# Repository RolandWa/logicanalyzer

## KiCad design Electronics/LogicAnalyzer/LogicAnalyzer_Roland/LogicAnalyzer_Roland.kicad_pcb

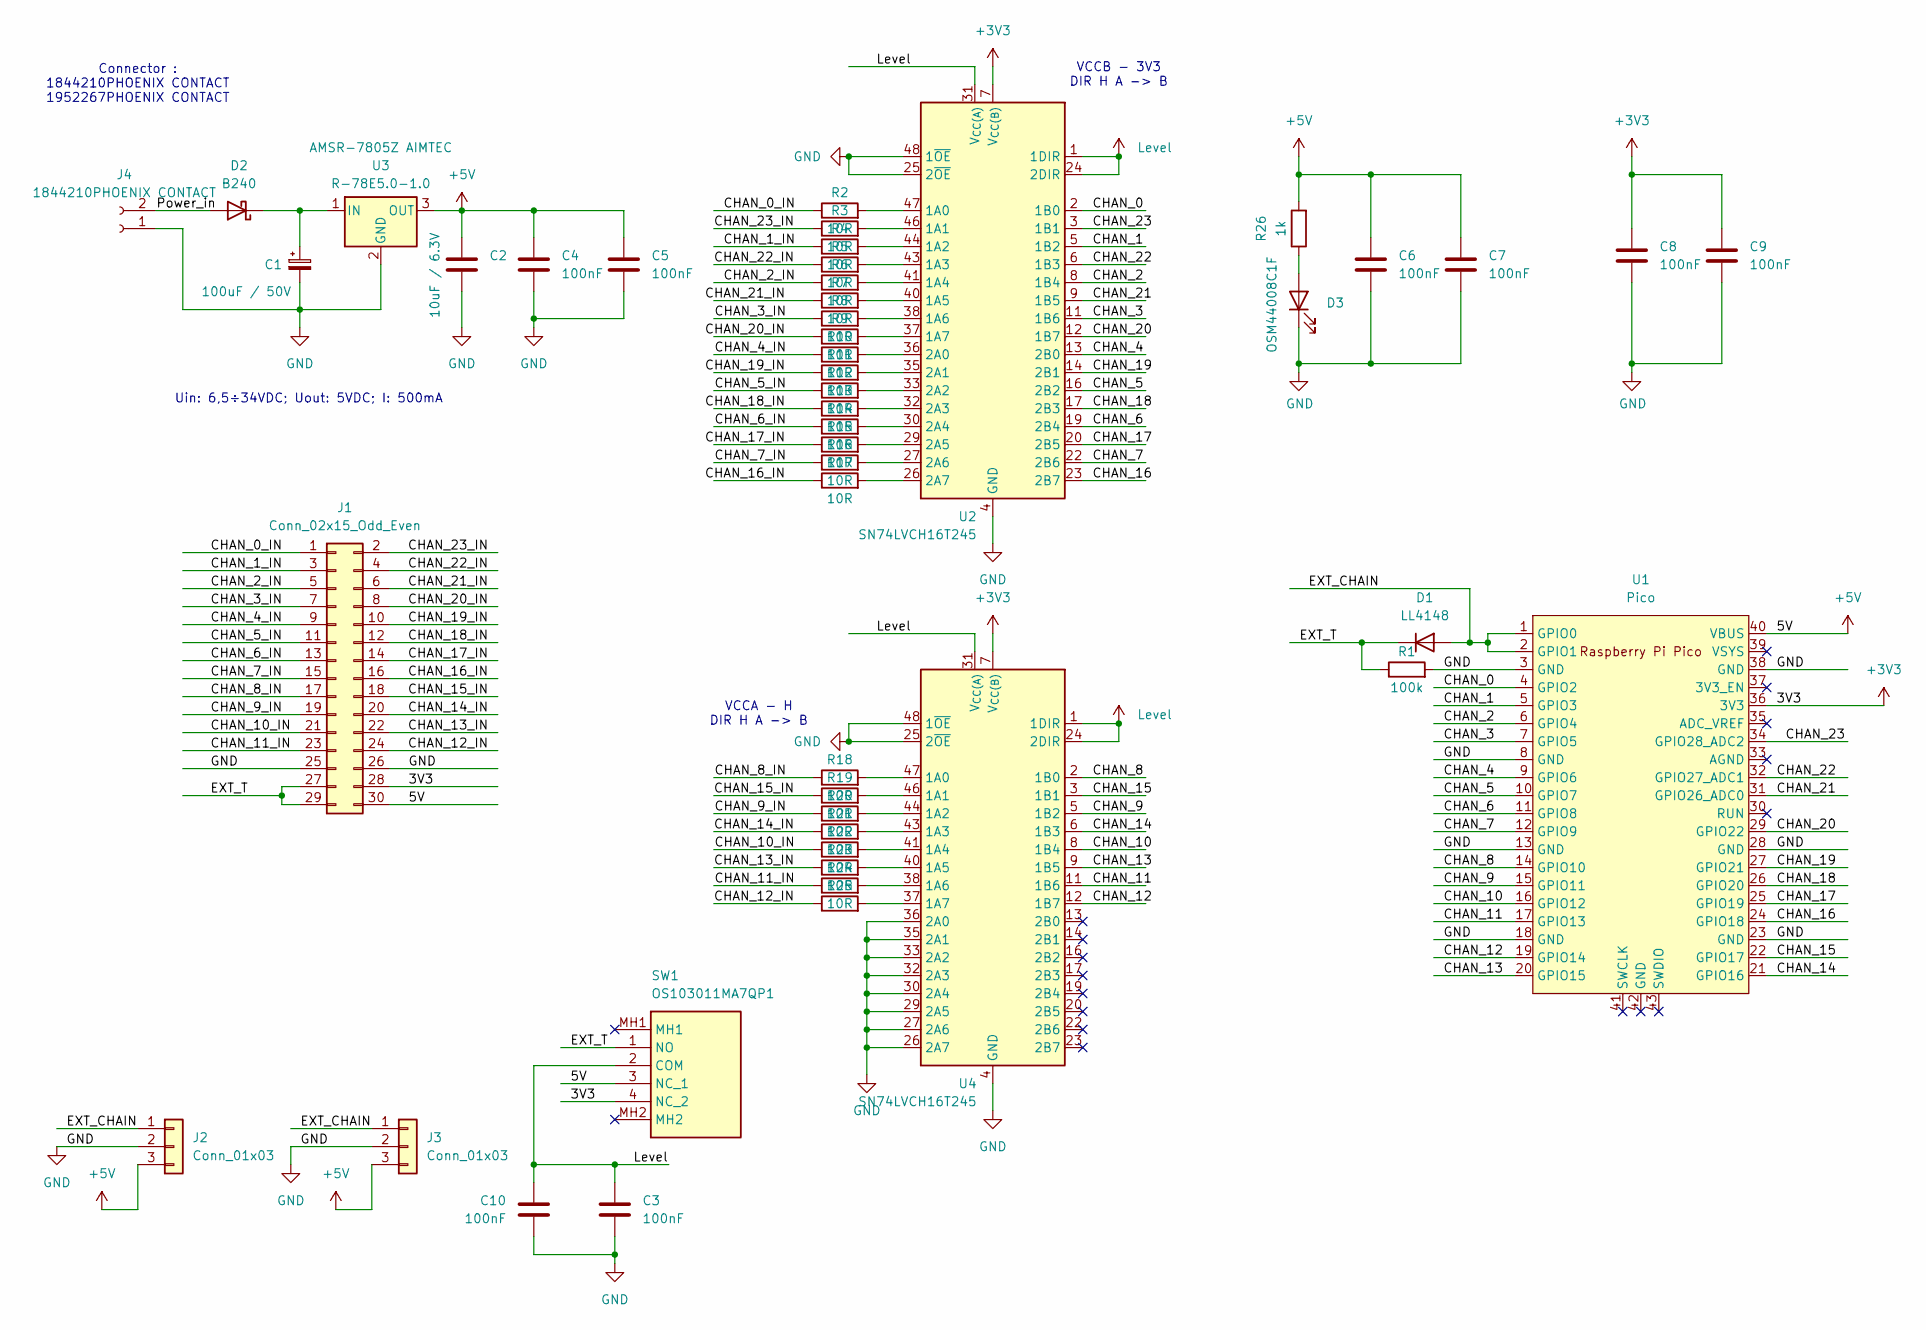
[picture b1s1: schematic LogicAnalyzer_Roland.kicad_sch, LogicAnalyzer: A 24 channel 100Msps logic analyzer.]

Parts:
C1: 100uF / 50V; CP_Radial_D8.0mm_P3.50mm
C2: 10uF / 6.3V; C_0805_2012Metric
C3, C4, C5, C6, C7, C8, C9, C10: 100nF; C_0603_1608Metric
D1: LL4148; D_MiniMELF
D2: B240; D_SMB
D3: OSM44008C1F; LED_OptoSupply_OSXX4008C1F_4x1.4mm_Horizontal
J1: Conn_02x15_Odd_Even; PinSocket_2x15_P2.54mm_Horizontal
J2: Conn_01x03; PinSocket_1x03_P2.54mm_Horizontal
J3: Conn_01x03; PinHeader_1x03_P2.54mm_Horizontal
J4: 1844210PHOENIX CONTACT; PhoenixContact_MC_1,5_2-G-3.5_1x02_P3.50mm_Horizontal
R1: 100k; R_0402_1005Metric
R2, R3, R4, R5, R6, R7, R8, R9, R10, R11, R12, R13, R14, R15, R16, R17, R18, R19, R20, R21, R22, R23, R24, R25: 10R; R_0402_1005Metric
R26: 1k; R_0402_1005Metric
SW1: OS103011MA7QP1; Manufacturer_Part_Number OS103011MA7QP1; Mouser Part Number 611-OS103011MA7QP1
U1: Pico; RPi_Pico_SMD_TH
U2, U4: SN74LVCH16T245; TSSOP-48_6.1x12.5mm_P0.5mm
U3: R-78E5.0-1.0; Converter_DCDC_RECOM_R-78E-0.5_THT

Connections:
+3V3: C8.1, C9.1, J1.28, SW1.4 (NC_2), U1.36 (3V3), U2.7 (V_{CC(B)}), U2.18 (V_{CC(B)}), U4.7 (V_{CC(B)}), U4.18 (V_{CC(B)})
+5V: C2.1, C4.1, C5.1, C6.1, C7.1, J1.30, J2.3, J3.3, R26.2, SW1.3 (NC_1), U1.40 (VBUS), U3.3 (OUT)
/CHAN_0: U1.4 (GPIO2), U2.2 (1B0)
/CHAN_0_IN: J1.1, R2.1
/CHAN_1: U1.5 (GPIO3), U2.5 (1B2)
/CHAN_1_IN: J1.3, R4.1
/CHAN_2: U1.6 (GPIO4), U2.8 (1B4)
/CHAN_2_IN: J1.5, R6.1
/CHAN_3: U1.7 (GPIO5), U2.11 (1B6)
/CHAN_3_IN: J1.7, R8.1
/CHAN_4: U1.9 (GPIO6), U2.13 (2B0)
/CHAN_4_IN: J1.9, R10.1
/CHAN_5: U1.10 (GPIO7), U2.16 (2B2)
/CHAN_5_IN: J1.11, R12.1
/CHAN_6: U1.11 (GPIO8), U2.19 (2B4)
/CHAN_6_IN: J1.13, R14.1
/CHAN_7: U1.12 (GPIO9), U2.22 (2B6)
/CHAN_7_IN: J1.15, R16.1
/CHAN_8: U1.14 (GPIO10), U4.2 (1B0)
/CHAN_8_IN: J1.17, R18.1
/CHAN_9: U1.15 (GPIO11), U4.5 (1B2)
/CHAN_9_IN: J1.19, R20.1
/CHAN_10: U1.16 (GPIO12), U4.8 (1B4)
/CHAN_10_IN: J1.21, R22.1
/CHAN_11: U1.17 (GPIO13), U4.11 (1B6)
/CHAN_11_IN: J1.23, R24.1
/CHAN_12: U1.19 (GPIO14), U4.12 (1B7)
/CHAN_12_IN: J1.24, R25.1
/CHAN_13: U1.20 (GPIO15), U4.9 (1B5)
/CHAN_13_IN: J1.22, R23.1
/CHAN_14: U1.21 (GPIO16), U4.6 (1B3)
/CHAN_14_IN: J1.20, R21.1
/CHAN_15: U1.22 (GPIO17), U4.3 (1B1)
/CHAN_15_IN: J1.18, R19.1
/CHAN_16: U1.24 (GPIO18), U2.23 (2B7)
/CHAN_16_IN: J1.16, R17.1
/CHAN_17: U1.25 (GPIO19), U2.20 (2B5)
/CHAN_17_IN: J1.14, R15.1
/CHAN_18: U1.26 (GPIO20), U2.17 (2B3)
/CHAN_18_IN: J1.12, R13.1
/CHAN_19: U1.27 (GPIO21), U2.14 (2B1)
/CHAN_19_IN: J1.10, R11.1
/CHAN_20: U1.29 (GPIO22), U2.12 (1B7)
/CHAN_20_IN: J1.8, R9.1
/CHAN_21: U1.31 (GPIO26_ADC0), U2.9 (1B5)
/CHAN_21_IN: J1.6, R7.1
/CHAN_22: U1.32 (GPIO27_ADC1), U2.6 (1B3)
/CHAN_22_IN: J1.4, R5.1
/CHAN_23: U1.34 (GPIO28_ADC2), U2.3 (1B1)
/CHAN_23_IN: J1.2, R3.1
/EXT_CHAIN: D1.2 (A), J2.1, J3.1, U1.1 (GPIO0), U1.2 (GPIO1)
/EXT_T: D1.1 (K), J1.27, J1.29, R1.1, SW1.1 (NO)
/Power_in: D2.2 (A), J4.2
GND: C1.2, C2.2, C3.2, C4.2, C5.2, C6.2, C7.2, C8.2, C9.2, C10.2, D3.1 (K), J1.25, J1.26, J2.2, J3.2, J4.1, R1.2, U1.3 (GND), U1.8 (GND), U1.13 (GND), U1.18 (GND), U1.23 (GND), U1.28 (GND), U1.38 (GND), U2.4 (GND), U2.10 (GND), U2.15 (GND), U2.21 (GND), U2.25 (2~OE), U2.28 (GND), U2.34 (GND), U2.39 (GND), U2.45 (GND), U2.48 (1~OE), U3.2 (GND), U4.4 (GND), U4.10 (GND), U4.15 (GND), U4.21 (GND), U4.25 (2~OE), U4.26 (2A7), U4.27 (2A6), U4.28 (GND), U4.29 (2A5), U4.30 (2A4), U4.32 (2A3), U4.33 (2A2), U4.34 (GND), U4.35 (2A1), U4.36 (2A0), U4.39 (GND), U4.45 (GND), U4.48 (1~OE)
Level: C3.1, C10.1, SW1.2 (COM), U2.1 (1DIR), U2.24 (2DIR), U2.31 (V_{CC(A)}), U2.42 (V_{CC(A)}), U4.1 (1DIR), U4.24 (2DIR), U4.31 (V_{CC(A)}), U4.42 (V_{CC(A)})
unnamed: C1.1, D2.1 (K), U3.1 (IN)
unnamed: D3.2 (A), R26.1
unnamed: R2.2, U2.47 (1A0)
unnamed: R3.2, U2.46 (1A1)
unnamed: R4.2, U2.44 (1A2)
unnamed: R5.2, U2.43 (1A3)
unnamed: R6.2, U2.41 (1A4)
unnamed: R7.2, U2.40 (1A5)
unnamed: R8.2, U2.38 (1A6)
unnamed: R9.2, U2.37 (1A7)
unnamed: R10.2, U2.36 (2A0)
unnamed: R11.2, U2.35 (2A1)
unnamed: R12.2, U2.33 (2A2)
unnamed: R13.2, U2.32 (2A3)
unnamed: R14.2, U2.30 (2A4)
unnamed: R15.2, U2.29 (2A5)
unnamed: R16.2, U2.27 (2A6)
unnamed: R17.2, U2.26 (2A7)
unnamed: R18.2, U4.47 (1A0)
unnamed: R19.2, U4.46 (1A1)
unnamed: R20.2, U4.44 (1A2)
unnamed: R21.2, U4.43 (1A3)
unnamed: R22.2, U4.41 (1A4)
unnamed: R23.2, U4.40 (1A5)
unnamed: R24.2, U4.38 (1A6)
unnamed: R25.2, U4.37 (1A7)

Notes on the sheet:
VCCB - 3V3 DIR H A -> B
Connector : 1844210PHOENIX CONTACT 1952267PHOENIX CONTACT
Uin: 6,5÷34VDC; Uout: 5VDC; I: 500mA
VCCA - H DIR H A -> B

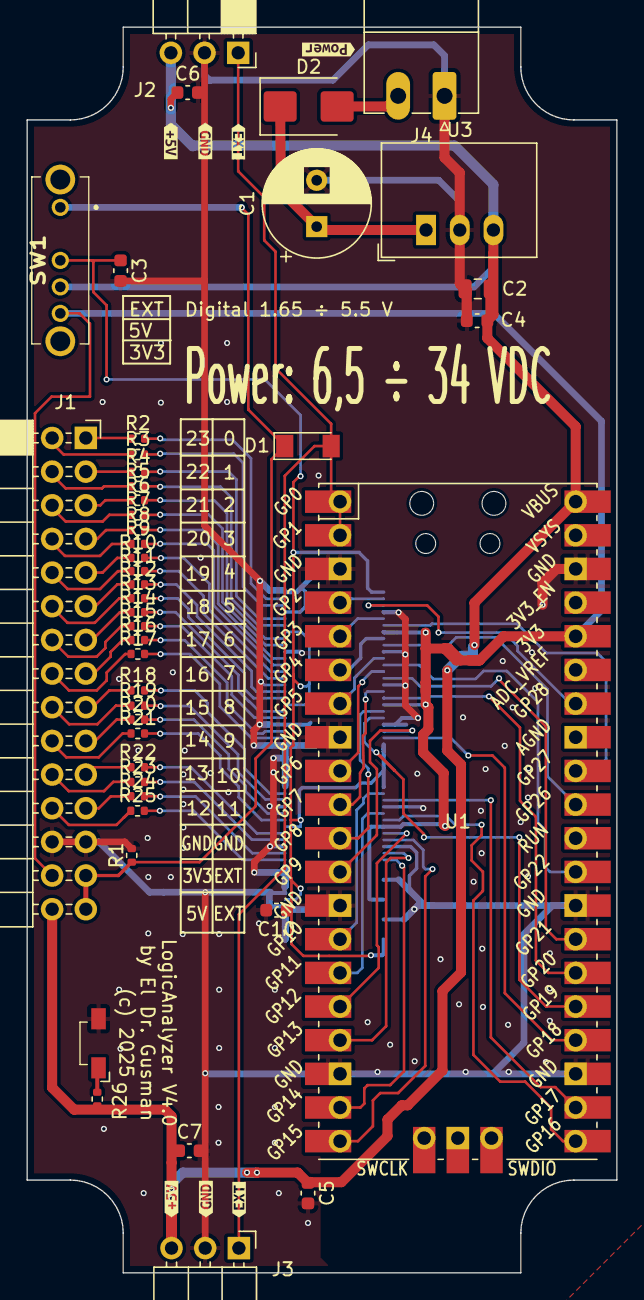
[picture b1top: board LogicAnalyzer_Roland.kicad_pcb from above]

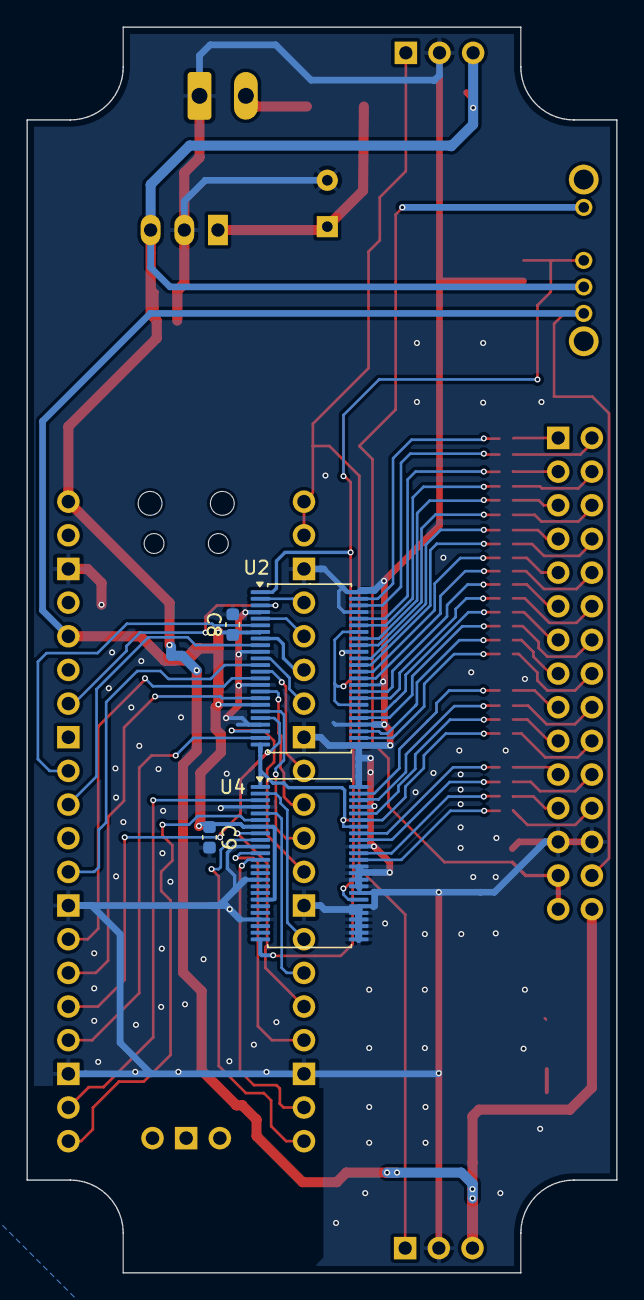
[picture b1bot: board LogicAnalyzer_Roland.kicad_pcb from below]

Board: 2 copper layers, 44.5 x 94.0 mm, 55 parts (4 on the bottom side), 81 nets.

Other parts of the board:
kibuzzard-679CD50C, kibuzzard-679CD50C#2: G***; kibuzzard-679CD50C
kibuzzard-679CD538, kibuzzard-679CD538#2: G***; kibuzzard-679CD538
kibuzzard-679CD548, kibuzzard-679CD548#2: G***; kibuzzard-679CD548
kibuzzard-679CD658: G***; kibuzzard-679CD658

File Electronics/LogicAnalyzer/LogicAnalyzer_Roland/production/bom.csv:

Designator,Footprint,Quantity,Value,LCSC Part #
C1,CP_Radial_D8.0mm_P3.50mm,1,100uF / 50V,
"C10, C3, C4, C5, C6, C7, C8, C9",0603,8,100nF,
C2,0805,1,10uF / 6.3V,
D1,D_MiniMELF,1,LL4148,
D2,D_SMB,1,B240,
D3,LED_OptoSupply_OSXX4008C1F_4x1.4mm_Horizontal,1,OSM44008C1F,
J1,PinSocket_2x15_P2.54mm_Horizontal,1,Conn_02x15_Odd_Even,
J2,PinSocket_1x03_P2.54mm_Horizontal,1,Conn_01x03,
J3,PinHeader_1x03_P2.54mm_Horizontal,1,Conn_01x03,
J4,"PhoenixContact_MC_1,5_2-G-3.5_1x02_P3.50mm_Horizontal",1,2EDGRC-5.0-02P-14-100Z(H),
R1,0402,1,100k,
"R10, R11, R12, R13, R14, R15, R16, R17, R18, R19, R2, R20, R21, R22, R23, R24, R25, R3, R4, R5, R6, R7, R8, R9",0402,24,10R,
R26,0402,1,1k,
SW1,OS103011MA7QP1,1,OS103011MA7QP1,
U1,RPi_Pico_SMD_TH,1,Pico,
"U2, U4",TSSOP-48_6.1x12.5mm_P0.5mm,2,SN74LVCH16T245,
U3,Converter_DCDC_RECOM_R-78E-0.5_THT,1,R-78E5.0-1.0,

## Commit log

2025-03-13 Create new PCB design use the KiCad, use SN74LVCH16T245 as a buffer, Plastic case Hammond 1591ATBU

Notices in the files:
Electronics/LogicAnalyzer/LogicAnalyzer_Roland/LogicAnalyzer_Roland.kicad_pcb:
(c) 2025
